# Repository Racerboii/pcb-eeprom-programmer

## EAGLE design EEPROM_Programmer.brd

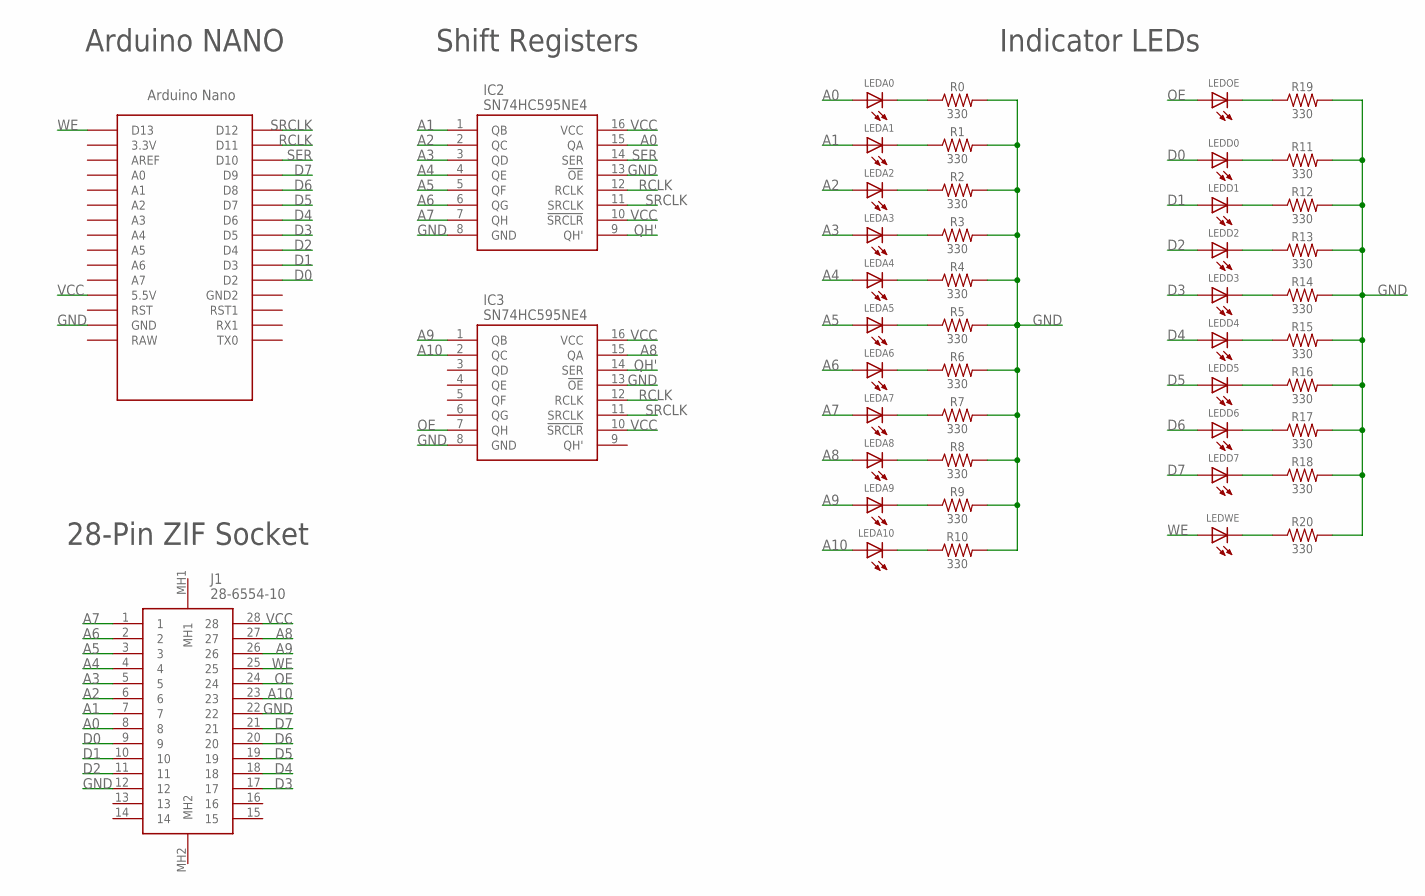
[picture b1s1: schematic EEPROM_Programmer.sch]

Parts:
IC2, IC3: SN74HC595NE4; DIP794W53P254L1930H508Q16N
J1: 28-6554-10; 28655410
LEDA0, LEDA1, LEDA2, LEDA3, LEDA4, LEDA5, LEDA6, LEDA7, LEDA8, LEDA9, LEDA10: LEDCHIPLED_1206; CHIPLED_1206
LEDD0, LEDD1, LEDD2, LEDD3, LEDD4, LEDD5, LEDD6, LEDD7: LEDCHIPLED_1206; CHIPLED_1206
LEDOE: LEDCHIPLED_1206; CHIPLED_1206
LEDWE: LEDCHIPLED_1206; CHIPLED_1206
R0, R1, R2, R3, R4, R5, R6, R7, R8, R9, R10, R11, R12, R13, R14, R15, R16, R17, R18, R19, R20: 330; 1206
U$1: NANO

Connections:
A0: IC2.15 (QA), J1.8, LEDA0.A
A1: IC2.1 (QB), J1.7, LEDA1.A
A2: IC2.2 (QC), J1.6, LEDA2.A
A3: IC2.3 (QD), J1.5, LEDA3.A
A4: IC2.4 (QE), J1.4, LEDA4.A
A5: IC2.5 (QF), J1.3, LEDA5.A
A6: IC2.6 (QG), J1.2, LEDA6.A
A7: IC2.7 (QH), J1.1, LEDA7.A
A8: IC3.15 (QA), J1.27, LEDA8.A
A9: IC3.1 (QB), J1.26, LEDA9.A
A10: IC3.2 (QC), J1.23, LEDA10.A
D0: J1.9, LEDD0.A, U$1.D2
D1: J1.10, LEDD1.A, U$1.D3
D2: J1.11, LEDD2.A, U$1.D4
D3: J1.17, LEDD3.A, U$1.D5
D4: J1.18, LEDD4.A, U$1.D6
D5: J1.19, LEDD5.A, U$1.D7
D6: J1.20, LEDD6.A, U$1.D8
D7: J1.21, LEDD7.A, U$1.D9
GND: IC2.8 (GND), IC2.13 (!OE), IC3.8 (GND), IC3.13 (!OE), J1.12, J1.22, R0.2, R1.2, R2.2, R3.2, R4.2, R5.2, R6.2, R7.2, R8.2, R9.2, R10.2, R11.2, R12.2, R13.2, R14.2, R15.2, R16.2, R17.2, R18.2, R19.2, R20.2, U$1.GND
unnamed: LEDA0.C, R0.1
unnamed: LEDA2.C, R2.1
unnamed: LEDA3.C, R3.1
unnamed: LEDA4.C, R4.1
unnamed: LEDA5.C, R5.1
unnamed: LEDA6.C, R6.1
unnamed: LEDA7.C, R7.1
unnamed: LEDA8.C, R8.1
unnamed: LEDA9.C, R9.1
unnamed: LEDA10.C, R10.1
unnamed: LEDA1.C, R1.1
unnamed: LEDD0.C, R11.1
unnamed: LEDD1.C, R12.1
unnamed: LEDD2.C, R13.1
unnamed: LEDD3.C, R14.1
unnamed: LEDD4.C, R15.1
unnamed: LEDD5.C, R16.1
unnamed: LEDD6.C, R17.1
unnamed: LEDD7.C, R18.1
unnamed: LEDOE.C, R19.1
unnamed: LEDWE.C, R20.1
OE: IC3.7 (QH), J1.24, LEDOE.A
QH': IC2.9 (QH'), IC3.14 (SER)
RCLK: IC2.12 (RCLK), IC3.12 (RCLK), U$1.D11
SER: IC2.14 (SER), U$1.D10
SRCLK: IC2.11 (SRCLK), IC3.11 (SRCLK), U$1.D12
VCC: IC2.10 (!SRCLR), IC2.16 (VCC), IC3.10 (!SRCLR), IC3.16 (VCC), J1.28, U$1.5V (5.5V)
WE: J1.25, LEDWE.A, U$1.D13

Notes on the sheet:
28-Pin ZIF Socket
Shift Registers
Arduino NANO
Indicator LEDs

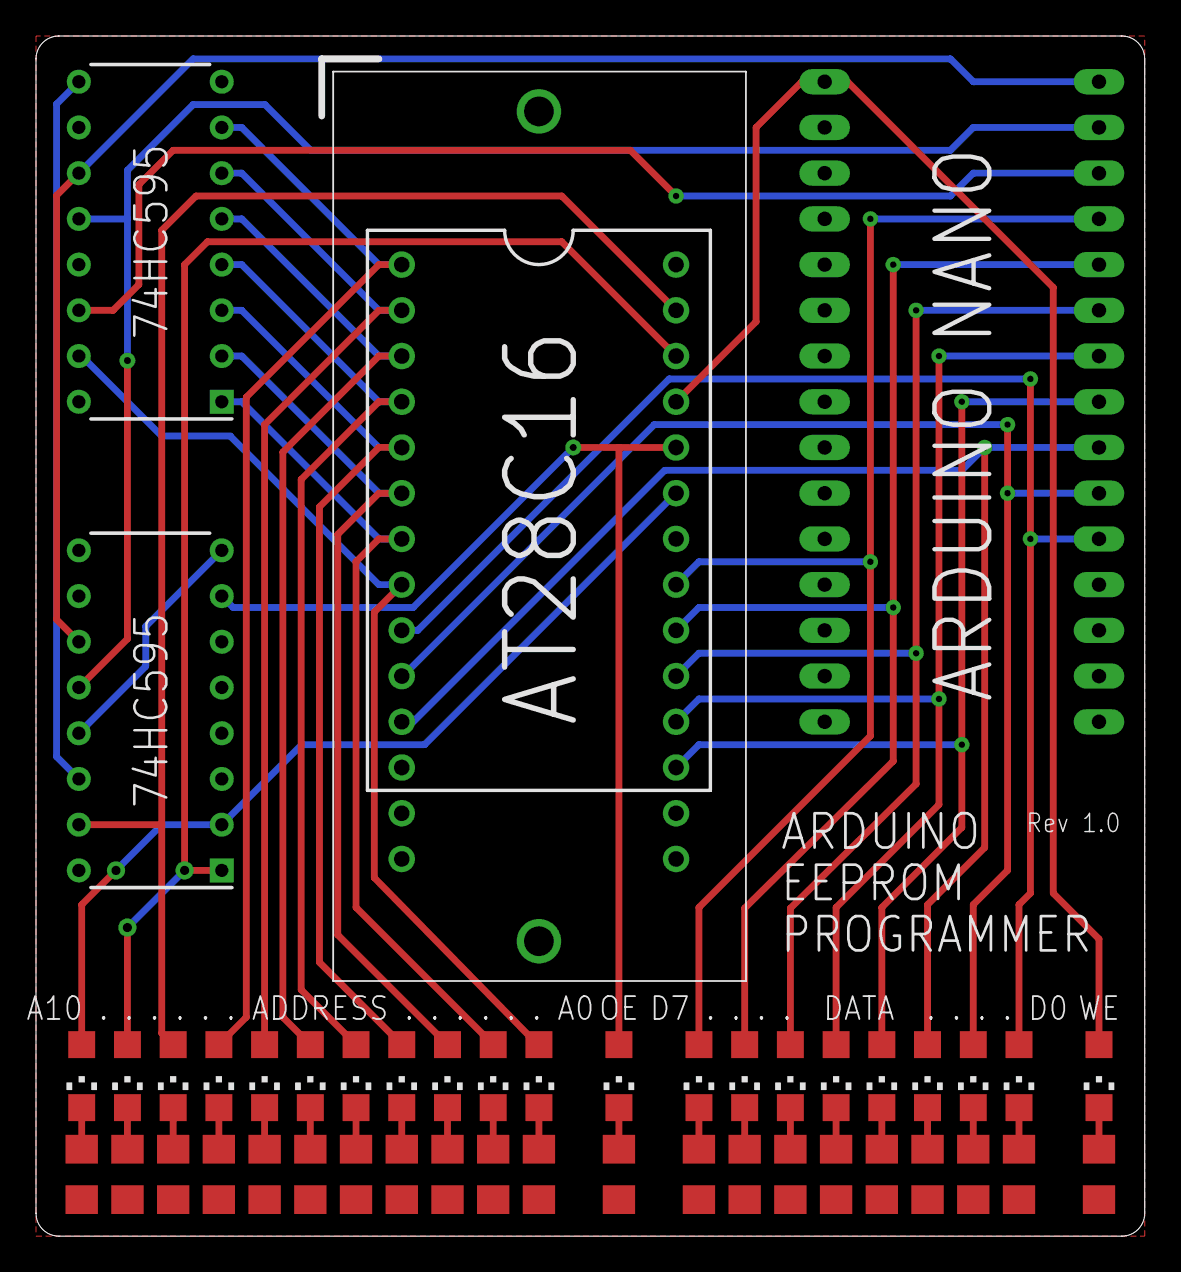
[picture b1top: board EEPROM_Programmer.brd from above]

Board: 2 copper layers, 61.6 x 66.7 mm, 46 parts (0 on the bottom side), 48 nets.

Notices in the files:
parts and their libraries:
SparkFun-Resistors: Licensing: Creative Commons ShareAlike 4.0 International - https://creativecommons.org/licenses/by-sa/4.0
